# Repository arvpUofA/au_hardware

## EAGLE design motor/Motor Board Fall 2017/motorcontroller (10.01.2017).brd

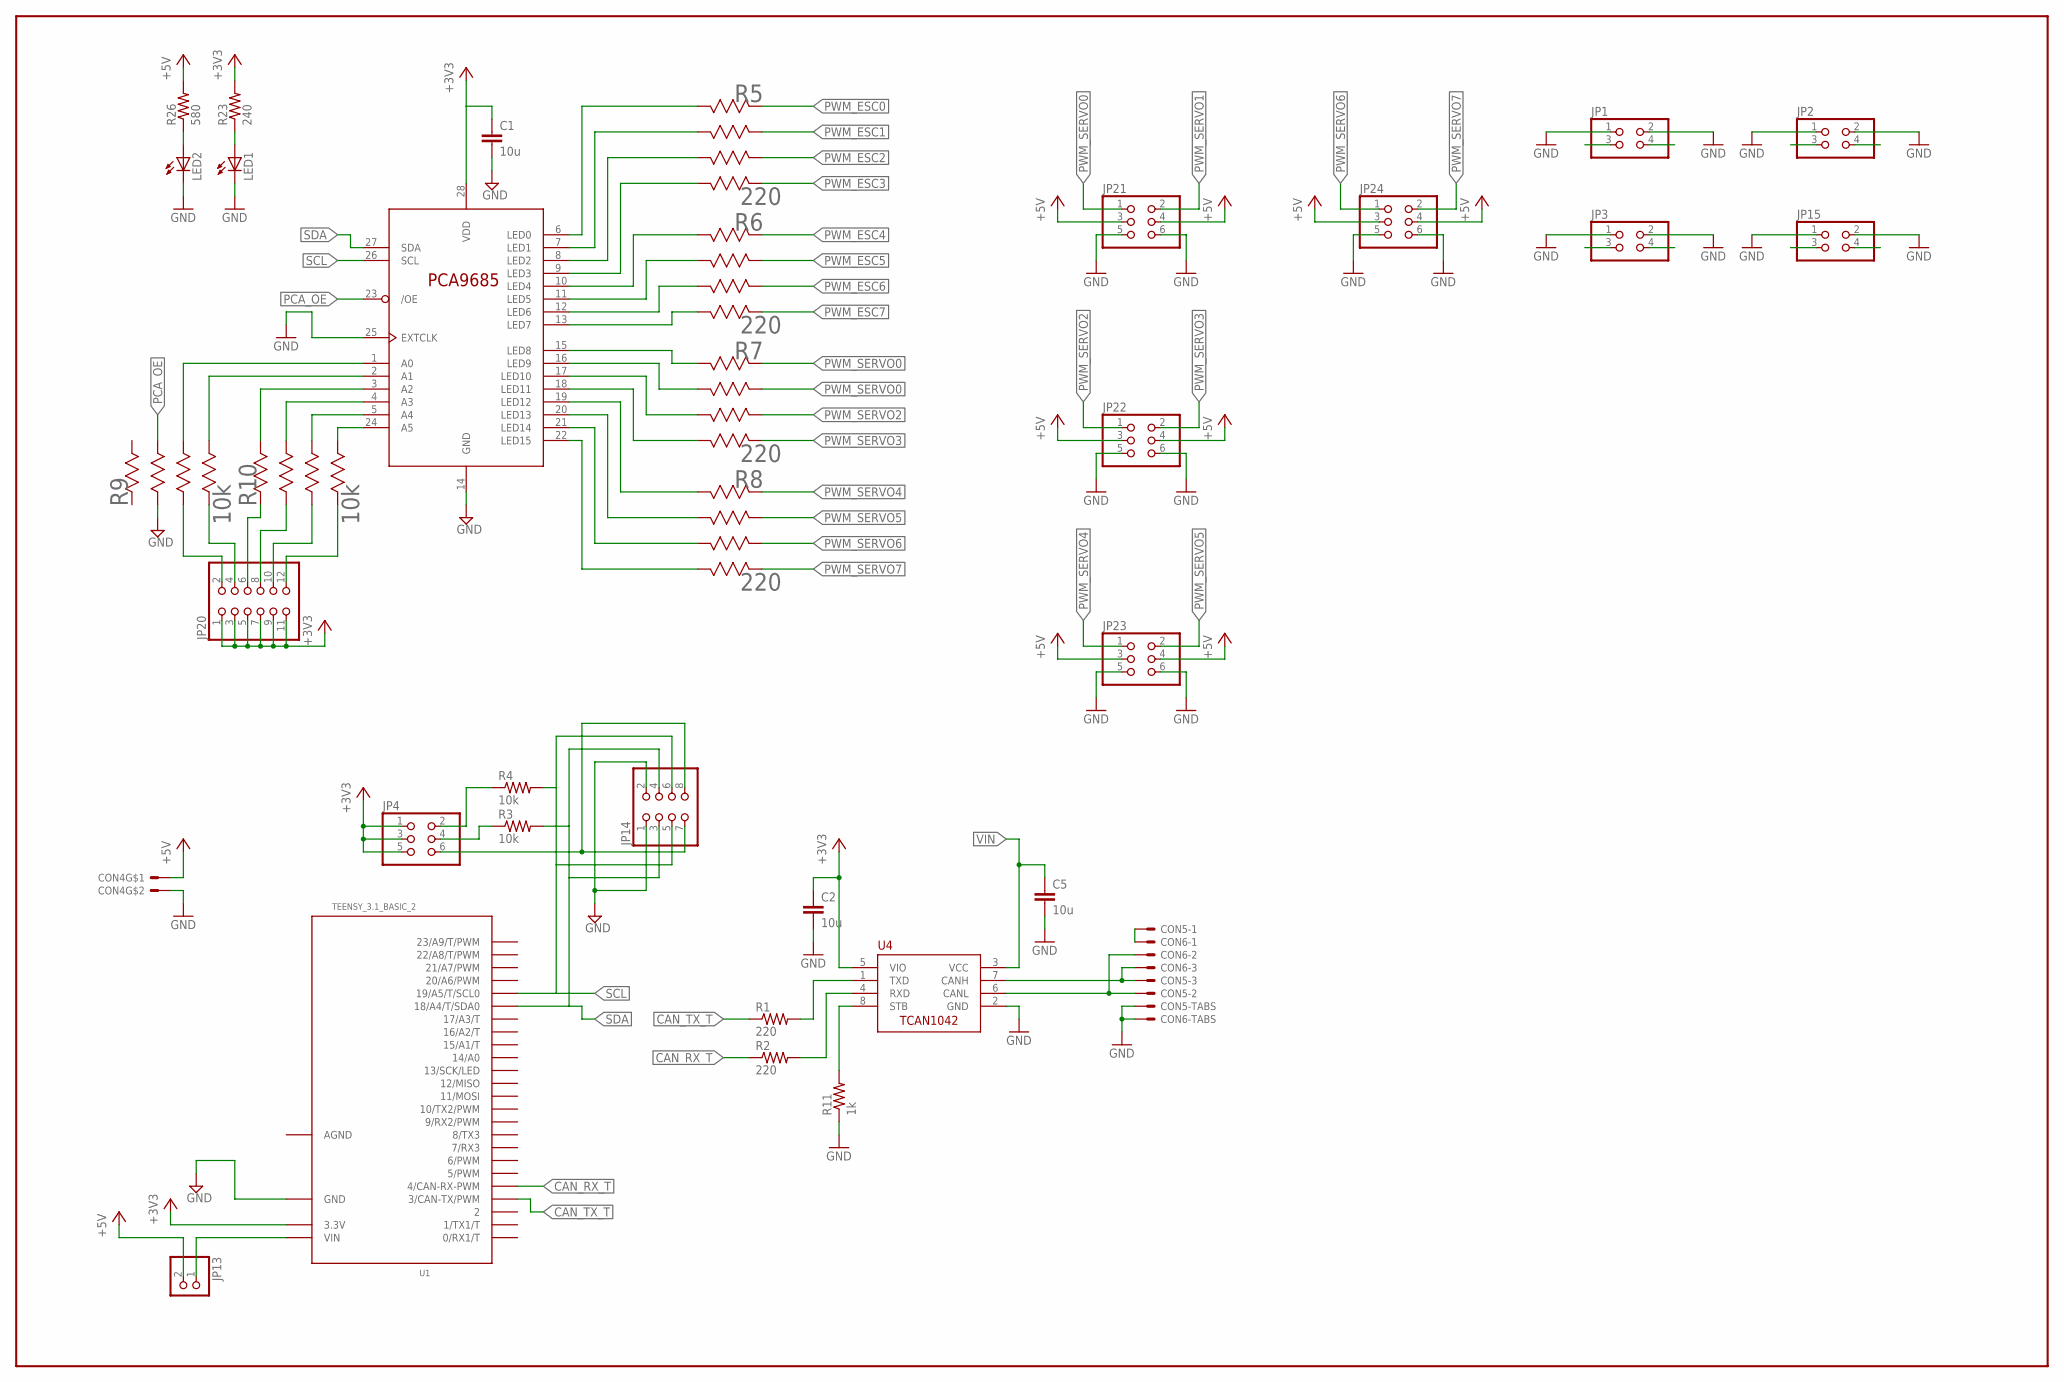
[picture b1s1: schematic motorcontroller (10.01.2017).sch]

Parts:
C1, C2, C5: 10u; C0805
CON4: MOLEX_5566-2; 5566-2
CON5, CON6: S3B-PH-SM4-TB
JP1, JP2, JP3, JP15: PINHD-2X2; 2X02
JP4, JP21, JP22, JP23, JP24: PINHD-2X3; 2X03
JP13: PINHD-1X2; 1X02
JP14: PINHD-2X4; 2X04
JP20: PINHD-2X6; 2X06
LED1, LED2: LEDCHIPLED_1206; CHIPLED_1206
R1, R2: 220; R0805
R3, R4: 10k; R1206
R5, R6, R7, R8: 220; EXBV8V-M
R9, R10: 10k; EXBV8V-M
R11: 1k; R0805
R23: 240; R1206
R26: 580; R1206
U1: TEENSY_3.1_BASIC_2
U2: PCA9685PW; TSSOP28
U4: TCAN1042HVDR; SO-8

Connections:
+3V3: C1.1, C2.1, JP4.1, JP4.3, JP4.5, JP20.1, JP20.3, JP20.5, JP20.7, JP20.9, JP20.11, R23.2, U1.3.3V, U2.28 (VDD), U4.5 (VIO)
+5V: CON4.1, JP13.2, JP21.3, JP21.4, JP22.3, JP22.4, JP23.3, JP23.4, JP24.3, JP24.4, R26.2
A0+1: JP20.2, R9.3 (35)
A1+1: JP20.4, R9.4 (47)
A2+1: JP20.6, R10.1 (11)
A3+1: JP20.8, R10.2 (23)
A4+1: JP20.10, R10.3 (35)
A5: JP20.12, R10.4 (47)
A6: R10.5 (58), U2.24 (A5)
A7: R10.6 (66), U2.5 (A4)
A8: R10.7 (74), U2.4 (A3)
A9: R10.8 (82), U2.3 (A2)
A10: R9.5 (58), U2.2 (A1)
A11: R9.6 (66), U2.1 (A0)
AGND: U1.AGND
CANH1: CON5.P$3, CON6.P$3, U4.7 (CANH)
CANL1: CON5.P$2, CON6.P$2, U4.6 (CANL)
CANSH1: CON5.P$1, CON6.P$1
CAN_RX1: R2.2, U4.4 (RXD)
CAN_RX_T: R2.1, U1.4 (4/CAN-RX-PWM)
CAN_TX2: R1.2, U4.1 (TXD)
CAN_TX_T: R1.1, U1.3 (3/CAN-TX/PWM)
GND: C1.2, C2.2, C5.2, CON4.2, CON5.P$4, CON5.P$5, CON6.P$4, CON6.P$5, JP1.1, JP1.2, JP2.1, JP2.2, JP3.1, JP3.2, JP14.1, JP14.2, JP15.1, JP15.2, JP21.5, JP21.6, JP22.5, JP22.6, JP23.5, JP23.6, JP24.5, JP24.6, LED1.C, LED2.C, R9.2 (23), R11.1, U1.GND, U2.14 (GND), U2.25 (EXTCLK), U4.2 (GND)
I2C_3V1: JP4.6, JP14.7, JP14.8
unnamed: LED1.A, R23.1
unnamed: LED2.A, R26.1
PCA_OE: R9.7 (74), U2.23 (/OE)
PWM_CH16: R5.8 (82), U2.6 (LED0)
PWM_CH17: R5.7 (74), U2.7 (LED1)
PWM_CH18: R5.6 (66), U2.8 (LED2)
PWM_CH19: R5.5 (58), U2.9 (LED3)
PWM_CH20: R6.8 (82), U2.10 (LED4)
PWM_CH21: R6.7 (74), U2.11 (LED5)
PWM_CH22: R6.6 (66), U2.12 (LED6)
PWM_CH23: R6.5 (58), U2.13 (LED7)
PWM_CH24: R7.8 (82), U2.15 (LED8)
PWM_CH25: R7.7 (74), U2.16 (LED9)
PWM_CH26: R7.6 (66), U2.17 (LED10)
PWM_CH27: R7.5 (58), U2.18 (LED11)
PWM_CH28: R8.8 (82), U2.19 (LED12)
PWM_CH29: R8.7 (74), U2.20 (LED13)
PWM_CH30: R8.6 (66), U2.21 (LED14)
PWM_CH31: R8.5 (58), U2.22 (LED15)
PWM_ESC0: JP15.4, R5.1 (11)
PWM_ESC1: JP15.3, R5.2 (23)
PWM_ESC2: JP1.4, R5.3 (35)
PWM_ESC3: JP1.3, R5.4 (47)
PWM_ESC4: JP2.4, R6.1 (11)
PWM_ESC5: JP2.3, R6.2 (23)
PWM_ESC6: JP3.4, R6.3 (35)
PWM_ESC7: JP3.3, R6.4 (47)
PWM_SERVO0: JP21.1, R7.1 (11)
PWM_SERVO1: JP21.2, R7.2 (23)
PWM_SERVO2: JP22.1, R7.3 (35)
PWM_SERVO3: JP22.2, R7.4 (47)
PWM_SERVO4: JP23.1, R8.1 (11)
PWM_SERVO5: JP23.2, R8.2 (23)
PWM_SERVO6: JP24.1, R8.3 (35)
PWM_SERVO7: JP24.2, R8.4 (47)
SCL: JP14.5, JP14.6, R4.2, U1.19/A5 (19/A5/T/SCL0), U2.26 (SCL)
SCL_3V1: JP4.2, R4.1
SDA: JP14.3, JP14.4, R3.2, U1.18/A4 (18/A4/T/SDA0), U2.27 (SDA)
SDA_3V1: JP4.4, R3.1
STB1: R11.2, U4.8 (STB)
VIN: C5.1, JP13.1, U1.VIN, U4.3 (VCC)

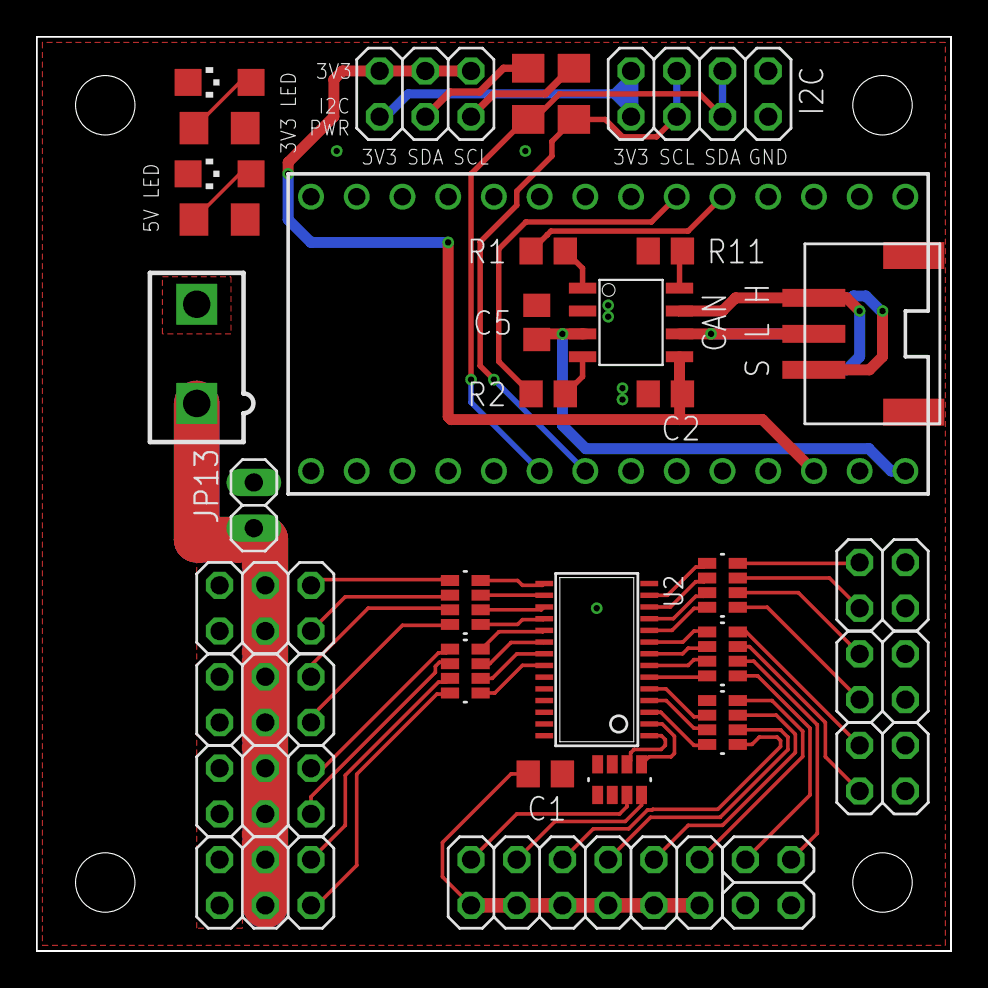
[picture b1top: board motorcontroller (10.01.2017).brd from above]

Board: 2 copper layers, 50.8 x 50.8 mm, 42 parts (1 on the bottom side), 64 nets.

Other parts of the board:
U$2, U$3, U$4, U$5: STAND-OFF
U$11: LETTER_L
U$12: DOCFIELD

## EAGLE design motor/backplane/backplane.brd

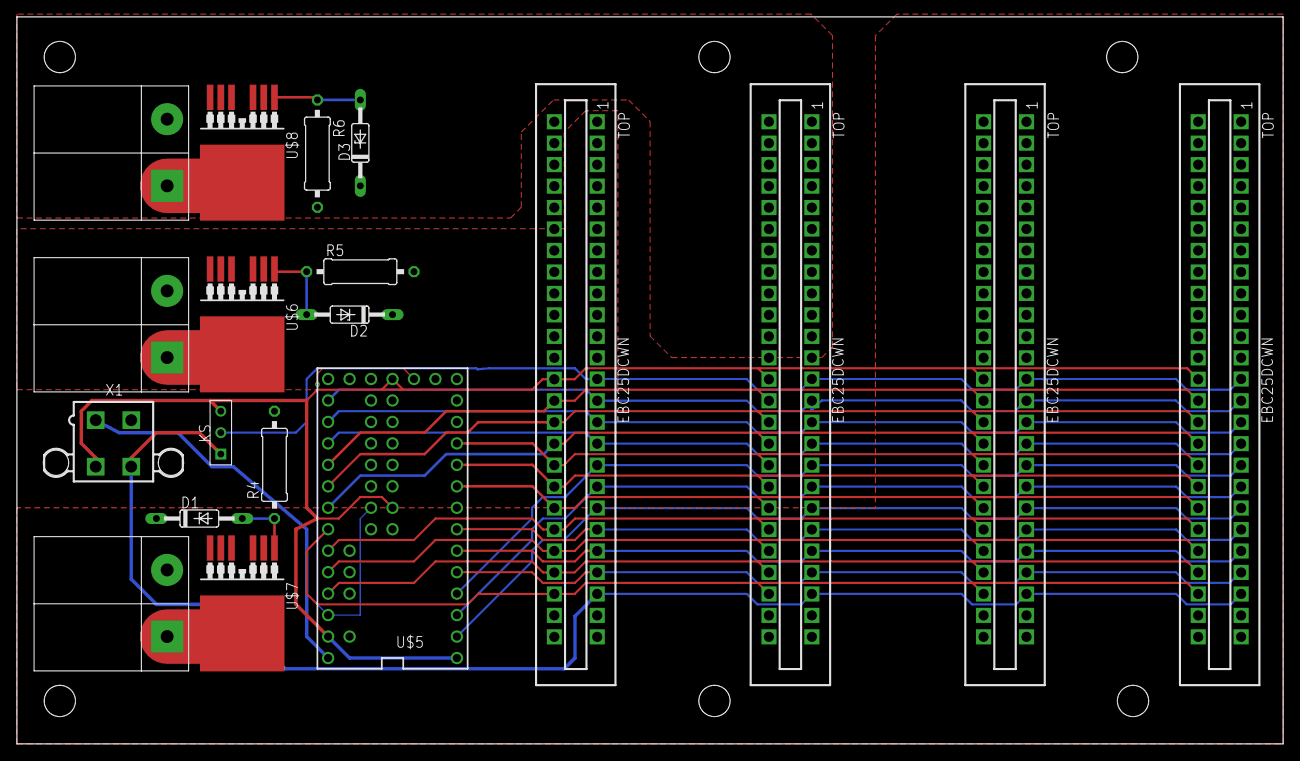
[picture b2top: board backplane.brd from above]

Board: 2 copper layers, 149.8 x 86.0 mm, 19 parts (0 on the bottom side), 34 nets.

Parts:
D1, D2, D3: BZX55; DO35Z10
R4, R5, R6: 100k; 0309/12
U$1, U$2, U$3: AND_PWR
U$4, U$9, U$10, U$11: CONN_50PIN
U$5: TEENSY_3.1-3.2_ALL_PINS&PADS; TEENSY_3.0-3.2_ALL_PINS_&_PADS
U$6, U$7, U$8: IPB180P04P4L-02; PG-TO263-7-3
U$12: KILL_SW
X1: 5566-4

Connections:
3.3V: U$4.A23, U$9.A23, U$10.A23, U$11.A23, U$12.P$1, X1.4
5V: U$5.VIN, X1.1
AGND: R4.2, R5.2, R6.2, U$1.GND, U$2.GND, U$3.GND, U$4.B1, U$4.B2, U$4.B3, U$4.B4, U$4.B5, U$4.B6, U$4.B7, U$4.B8, U$4.B9, U$4.B10, U$4.B11, U$4.B12, U$9.B1, U$9.B2, U$9.B3, U$9.B4, U$9.B5, U$9.B6, U$9.B7, U$9.B8, U$9.B9, U$9.B10, U$9.B11, U$9.B12, U$10.B1, U$10.B2, U$10.B3, U$10.B4, U$10.B5, U$10.B6, U$10.B7, U$10.B8, U$10.B9, U$10.B10, U$10.B11, U$10.B12, U$11.B1, U$11.B2, U$11.B3, U$11.B4, U$11.B5, U$11.B6, U$11.B7, U$11.B8, U$11.B9, U$11.B10, U$11.B11, U$11.B12
BAT+0: U$3.PWR, U$8.8
BAT+1: U$2.PWR, U$6.8
BAT+2: U$1.PWR, U$7.8
CS_X0: U$4.A16, U$5.16/A2, U$9.A16, U$10.A16, U$11.A16
CS_X1: U$4.B16, U$5.19/A5, U$9.B16, U$10.B16, U$11.B16
CS_Y0: U$4.A15, U$5.15/A1, U$9.A15, U$10.A15, U$11.A15
CS_Y1: U$4.B15, U$5.18/A4, U$9.B15, U$10.B15, U$11.B15
CS_Z0: U$4.A14, U$5.14/A0, U$9.A14, U$10.A14, U$11.A14
CS_Z1: U$4.B14, U$5.17/A3, U$9.B14, U$10.B14, U$11.B14
DIR_X0: U$4.A19, U$5.0, U$9.A19, U$10.A19, U$11.A19
DIR_X1: U$4.B19, U$5.7, U$9.B19, U$10.B19, U$11.B19
DIR_Y0: U$4.A18, U$5.1, U$9.A18, U$10.A18, U$11.A18
DIR_Y1: U$4.B18, U$5.8, U$9.B18, U$10.B18, U$11.B18
DIR_Z0: U$4.A17, U$5.2, U$9.A17, U$10.A17, U$11.A17
DIR_Z1: U$4.B17, U$5.9, U$9.B17, U$10.B17, U$11.B17
EN: U$4.B23, U$5.20/A6, U$9.B23, U$10.B23, U$11.B23
GND: U$4.B13, U$5.AGND, U$5.GND, U$5.GND1, U$5.GND2, U$9.B13, U$10.B13, U$11.B13, U$12.P$3, X1.3
KS: U$4.A13, U$9.A13, U$10.A13, U$11.A13, U$12.P$2
unnamed: U$5.3.3V, U$5.3.3V1, U$5.3.3V2
unnamed: D3.A, R6.1, U$8.1
unnamed: D2.A, R5.1, U$6.1
unnamed: D1.A, R4.1, U$7.1
PWM_X0: U$4.A22, U$5.3, U$9.A22, U$10.A22, U$11.A22
PWM_X1: U$4.B22, U$5.23/A9, U$9.B22, U$10.B22, U$11.B22
PWM_Y0: U$4.A21, U$5.4, U$9.A21, U$10.A21, U$11.A21
PWM_Y1: U$4.B21, U$5.22/A8, U$9.B21, U$10.B21, U$11.B21
PWM_Z0: U$4.A20, U$5.5, U$9.A20, U$10.A20, U$11.A20
PWM_Z1: U$4.B20, U$5.21/A7, U$9.B20, U$10.B20, U$11.B20
PWR0: D3.C, U$8.2, U$8.3, U$8.5, U$8.6, U$8.7, U$9.A1, U$9.A2, U$9.A3, U$9.A4, U$9.A5, U$9.A6, U$9.A7, U$9.A8, U$9.A9, U$9.A10, U$9.A11, U$9.A12
PWR1: D2.C, U$4.A1, U$4.A2, U$4.A3, U$4.A4, U$4.A5, U$4.A6, U$4.A7, U$4.A8, U$4.A9, U$4.A10, U$4.A11, U$4.A12, U$6.2, U$6.3, U$6.5, U$6.6, U$6.7
PWR2: D1.C, U$7.2, U$7.3, U$7.5, U$7.6, U$7.7, U$10.A1, U$10.A2, U$10.A3, U$10.A4, U$10.A5, U$10.A6, U$10.A7, U$10.A8, U$10.A9, U$10.A10, U$10.A11, U$10.A12

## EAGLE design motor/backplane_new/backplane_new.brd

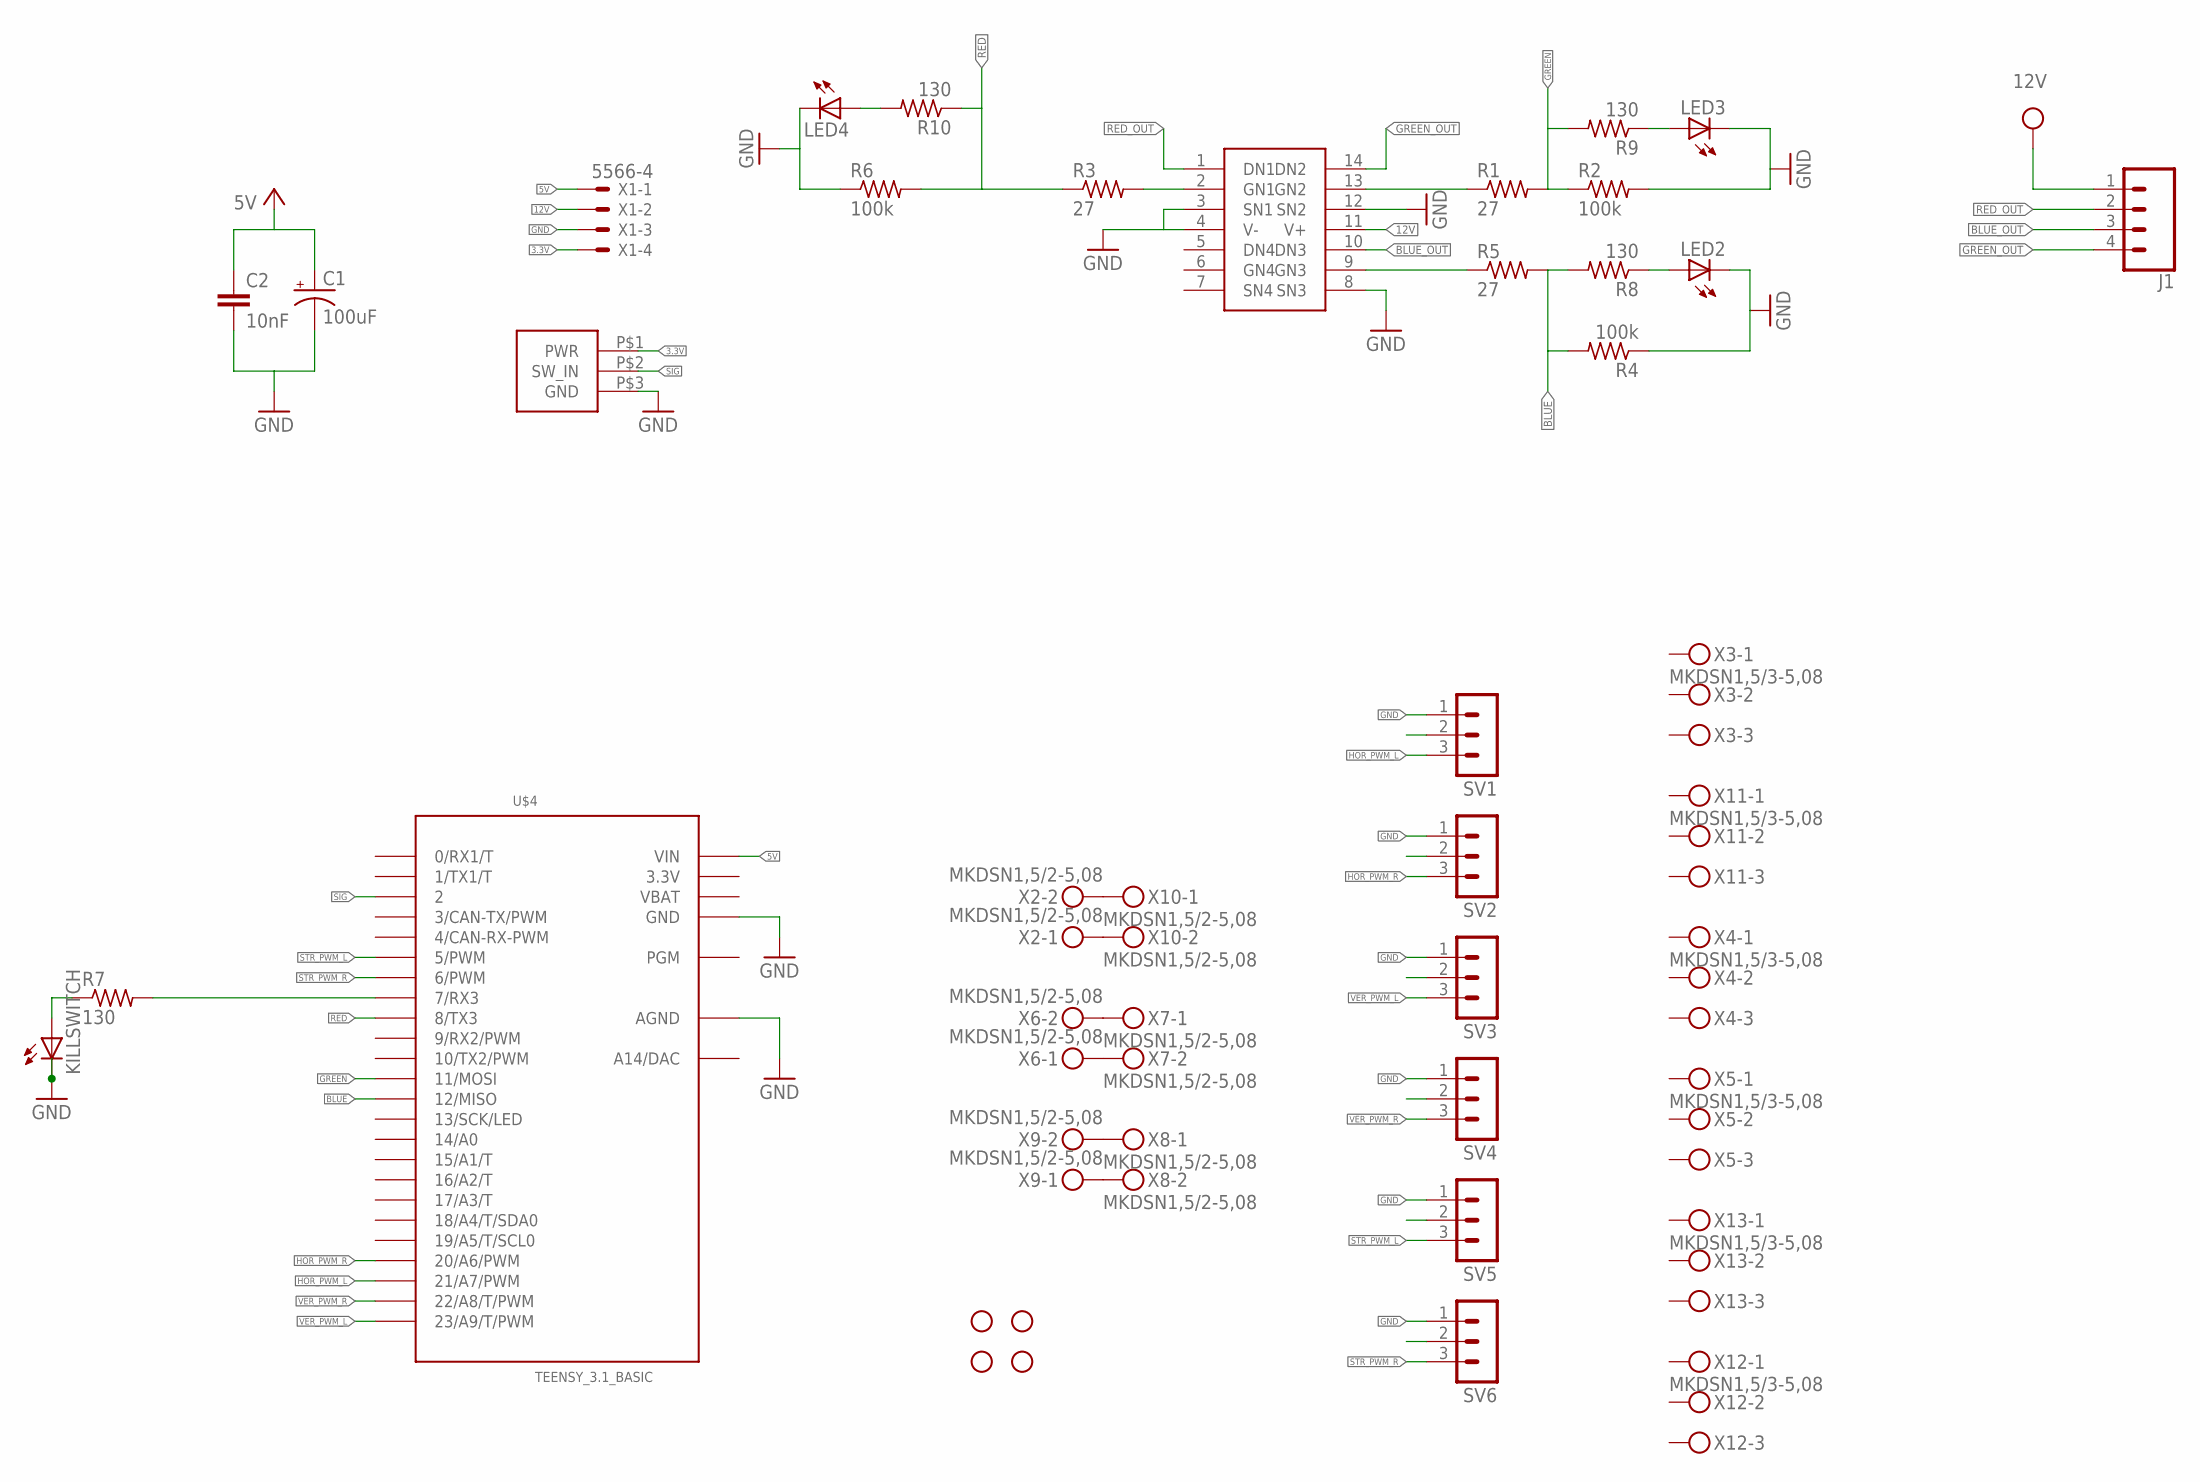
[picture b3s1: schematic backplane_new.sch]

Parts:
C1: 100uF; E5-10,5
C2: 10nF; C0805
H1, H2, H3, H5: STAND-OFF
J1: CONN_04POLAR; MOLEX-1X4
KILLSWITCH: LED5MM
LED2, LED3, LED4: LEDCHIP-LED0805; CHIP-LED0805
R1, R3, R5: 27; R0805
R2, R4, R6: 100k; R0805
R7, R8, R9, R10: 130; R0805
SV1, SV2, SV3, SV4, SV5, SV6: MA03-1
U$2: KILL_SW
U$3: ALD1160; DIL14
U$4: TEENSY_3.1_BASIC
X1: 5566-4
X2, X6, X7, X8, X9, X10: MKDSN1,5/2-5,08
X3, X4, X5, X11, X12, X13: MKDSN1,5/3-5,08

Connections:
3.3V: U$2.P$1 (PWR), U$4.3.3V, U$4.3.3V1 (3.3V), X1.4
5V: C1.+, C2.1, U$4.VIN, X1.1
12V: J1.1, U$3.11 (V+), X1.2
BLUE: R4.2, R5.2, R8.2, U$4.12 (12/MISO)
BLUE_OUT: J1.3, U$3.10 (DN3)
GND: C1.-, C2.2, KILLSWITCH.K (C), LED2.C, LED3.C, LED4.C, R2.2, R4.1, R6.1, SV1.1, SV2.1, SV3.1, SV4.1, SV5.1, SV6.1, U$2.P$3 (GND), U$3.3 (SN1), U$3.4 (V-), U$3.8 (SN3), U$3.12 (SN2), U$4.AGND, U$4.GND, U$4.GND1 (GND), X1.3
GREEN: R1.2, R2.1, R9.2, U$4.11 (11/MOSI)
GREEN_OUT: J1.4, U$3.14 (DN2)
HOR_PWM_L: SV1.3, U$4.21/A7 (21/A7/PWM)
HOR_PWM_R: SV2.3, U$4.20/A6 (20/A6/PWM)
unnamed: X2.1, X10.2
unnamed: X2.2, X10.1
unnamed: X6.2, X7.1
unnamed: X6.1, X7.2
unnamed: X8.2, X9.1
unnamed: X8.1, X9.2
unnamed: R7.2, U$4.7 (7/RX3)
unnamed: KILLSWITCH.A, R7.1
unnamed: R3.2, U$3.2 (GN1)
unnamed: R1.1, U$3.13 (GN2)
unnamed: R5.1, U$3.9 (GN3)
unnamed: LED2.A, R8.1
unnamed: LED4.A, R10.2
unnamed: LED3.A, R9.1
RED: R3.1, R6.2, R10.1, U$4.8 (8/TX3)
RED_OUT: J1.2, U$3.1 (DN1)
SIG: U$2.P$2 (SW_IN), U$4.2
STR_PWM_L: SV5.3, U$4.5 (5/PWM)
STR_PWM_R: SV6.3, U$4.6 (6/PWM)
VBAT: U$4.VBAT
VER_PWM_L: SV3.3, U$4.23/A9 (23/A9/T/PWM)
VER_PWM_R: SV4.3, U$4.22/A8 (22/A8/T/PWM)

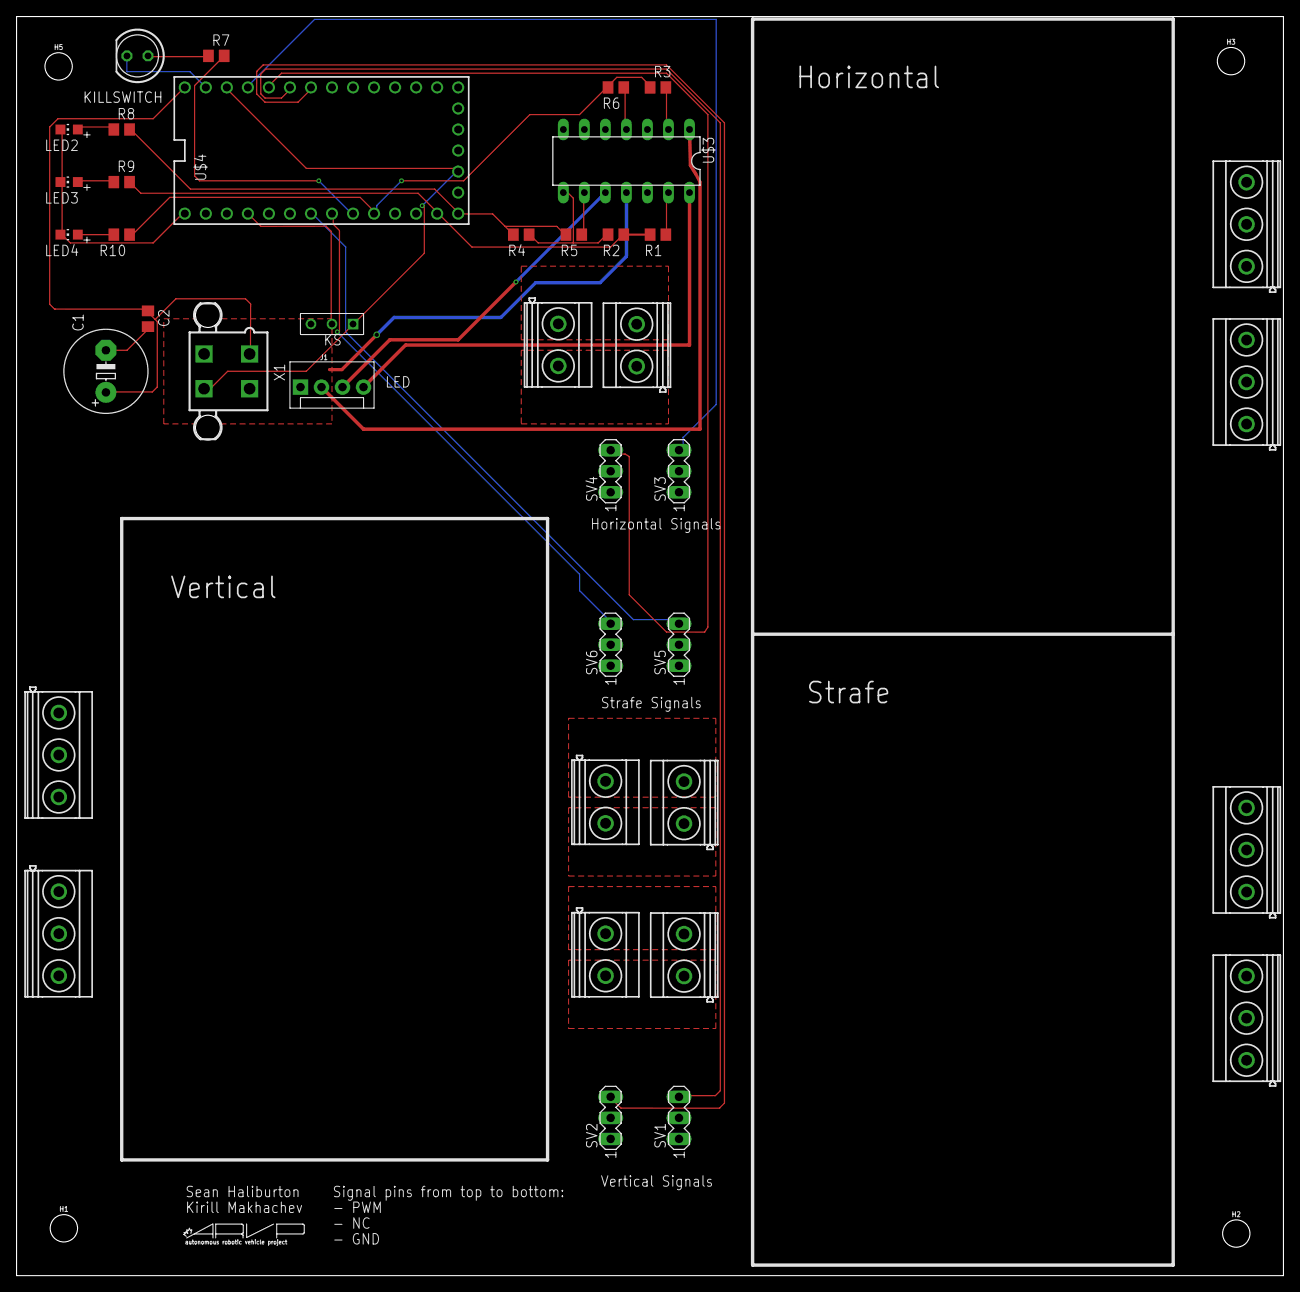
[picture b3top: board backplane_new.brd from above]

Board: 2 copper layers, 153.0 x 152.1 mm, 44 parts (0 on the bottom side), 31 nets.

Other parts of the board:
U$1: ARVP

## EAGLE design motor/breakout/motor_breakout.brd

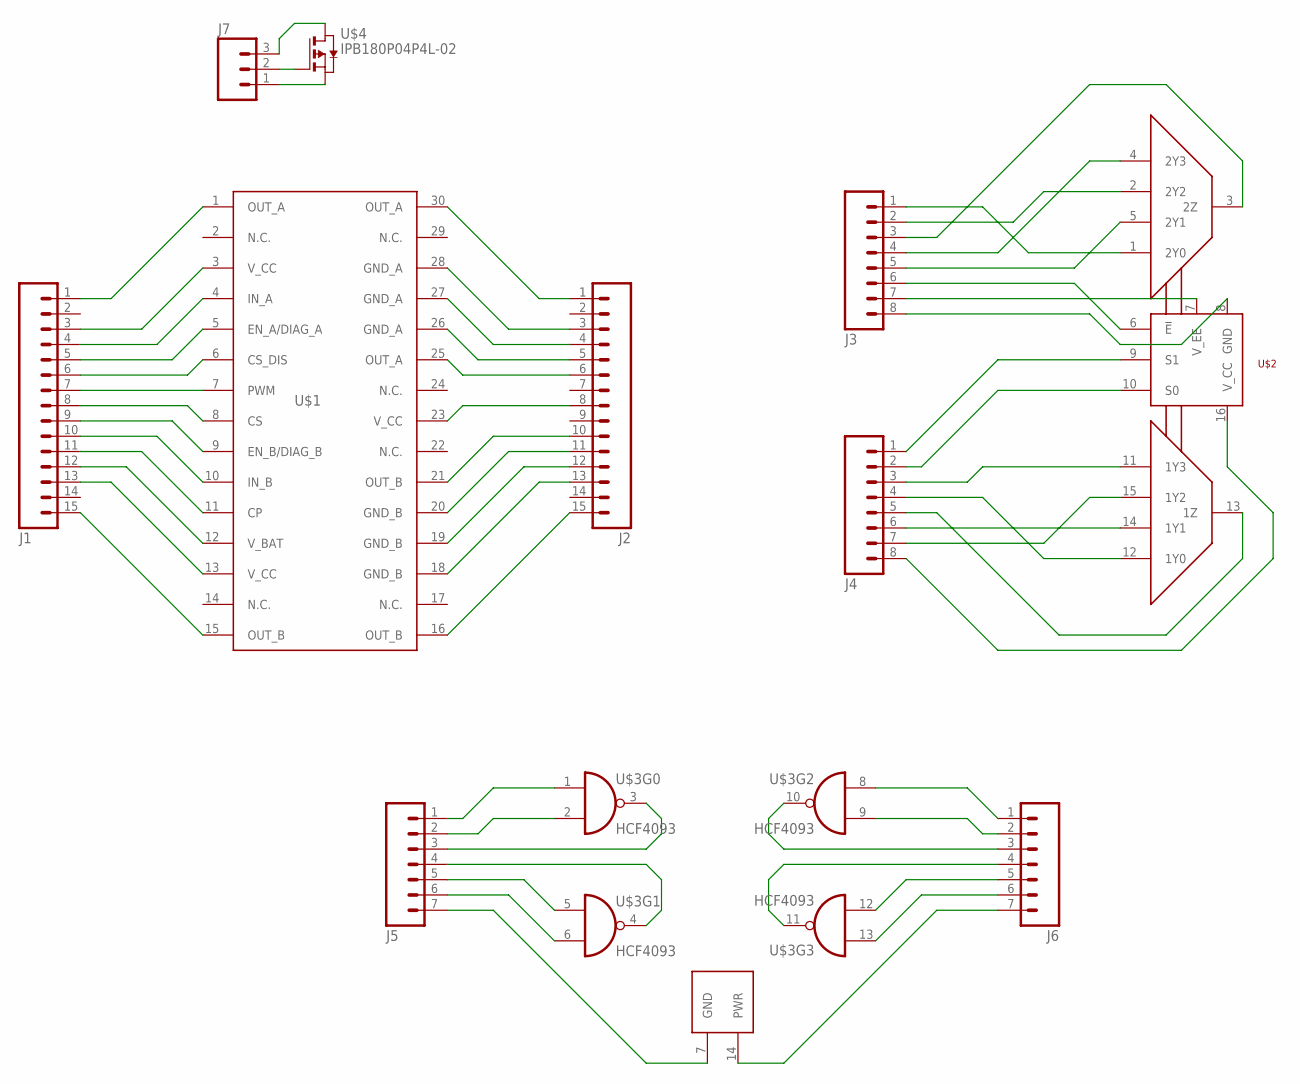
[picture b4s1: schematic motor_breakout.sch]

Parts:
J1, J2: M15; 1X15
J3, J4: M08SILK_FEMALE_PTH; 1X08
J5, J6: M07; 1X07
J7: M03PTH; 1X03
U$1: VNH5019A-E; MULTIPOWERSO-30
U$2: 74HC4052-Q100; SO16
U$3: HCF4093; SO14
U$4: IPB180P04P4L-02; PG-TO263-7-3

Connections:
GND_A: J2.3, J2.4, J2.5, U$1.26 (GND_A), U$1.27 (GND_A), U$1.28 (GND_A)
GND_B: J2.11, J2.12, J2.13, U$1.18 (GND_B), U$1.19 (GND_B), U$1.20 (GND_B)
unnamed: J1.7, U$1.7 (PWM)
unnamed: J7.2, U$4.1 (G)
unnamed: J1.8, U$1.8 (CS)
unnamed: J1.6, U$1.6 (CS_DIS)
unnamed: J1.9, U$1.9 (EN_B/DIAG_B)
unnamed: J1.5, U$1.5 (EN_A/DIAG_A)
unnamed: J1.4, U$1.4 (IN_A)
unnamed: J1.10, U$1.10 (IN_B)
unnamed: J1.11, U$1.11 (CP)
unnamed: J1.12, U$1.12 (V_BAT)
unnamed: J3.1, U$2.1 (2Y0)
unnamed: J3.2, U$2.2 (2Y2)
unnamed: J3.3, U$2.3 (2Z)
unnamed: J3.4, U$2.4 (2Y3)
unnamed: J3.5, U$2.5 (2Y1)
unnamed: J3.6, U$2.6 (!E)
unnamed: J3.7, U$2.7 (V_EE)
unnamed: J3.8, U$2.8 (GND)
unnamed: J4.1, U$2.9 (S1)
unnamed: J4.2, U$2.10 (S0)
unnamed: J4.3, U$2.11 (1Y3)
unnamed: J4.4, U$2.12 (1Y0)
unnamed: J4.5, U$2.13 (1Z)
unnamed: J4.6, U$2.14 (1Y1)
unnamed: J4.7, U$2.15 (1Y2)
unnamed: J4.8, U$2.16 (V_CC)
unnamed: J5.1, U$3.1 (I0)
unnamed: J5.2, U$3.2 (I1)
unnamed: J5.3, U$3.3 (O)
unnamed: J5.4, U$3.4 (O)
unnamed: J5.5, U$3.5 (I0)
unnamed: J5.6, U$3.6 (I1)
unnamed: J5.7, U$3.7 (GND)
unnamed: J6.1, U$3.8 (I0)
unnamed: J6.2, U$3.9 (I1)
unnamed: J6.3, U$3.10 (O)
unnamed: J6.4, U$3.11 (O)
unnamed: J6.5, U$3.12 (I1)
unnamed: J6.6, U$3.13 (I0)
unnamed: J6.7, U$3.14 (PWR)
unnamed: J7.1, U$4.2 (S), U$4.3 (S), U$4.5 (S), U$4.6 (S), U$4.7 (S)
unnamed: J7.3, U$4.8 (D)
OUT_A: J1.1, J2.1, J2.6, U$1.1 (OUT_A), U$1.25 (OUT_A), U$1.30 (OUT_A)
OUT_B: J1.15, J2.10, J2.15, U$1.15 (OUT_B), U$1.16 (OUT_B), U$1.21 (OUT_B)
VCC: J1.3, J1.13, J2.8, U$1.3 (V_CC), U$1.13 (V_CC), U$1.23 (V_CC)

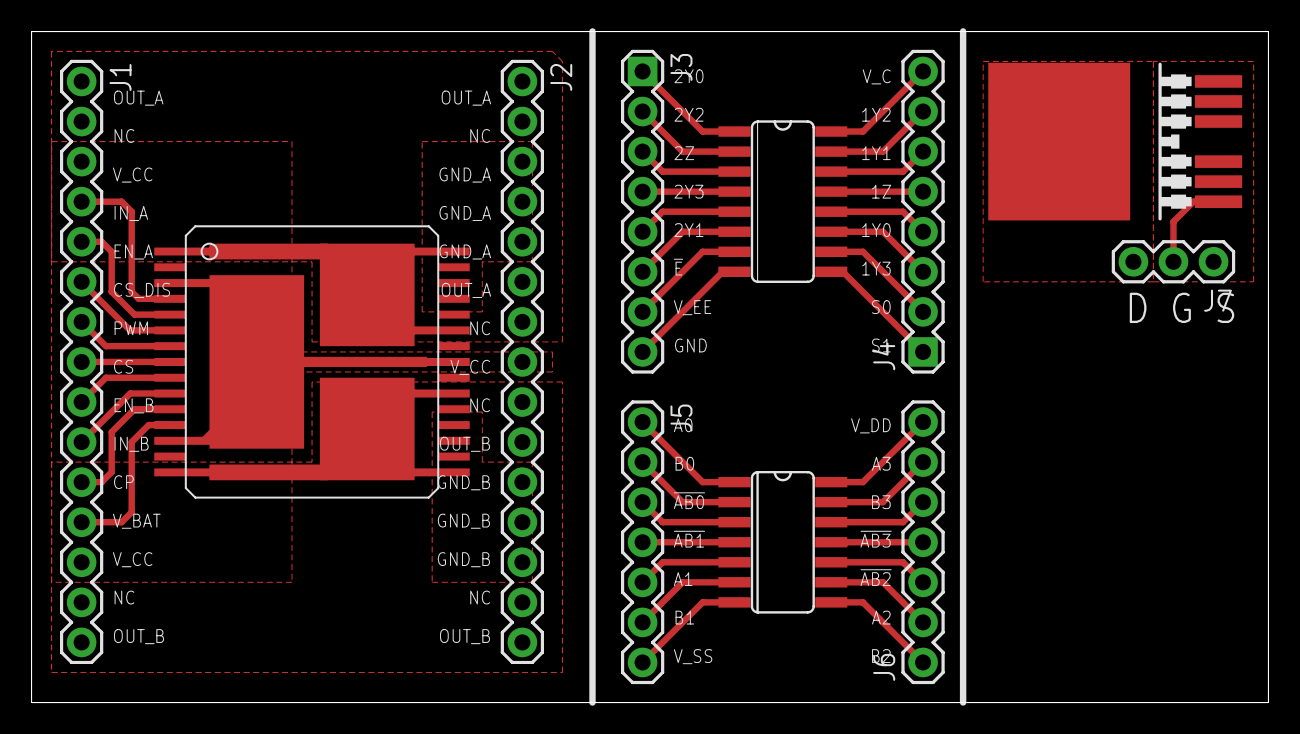
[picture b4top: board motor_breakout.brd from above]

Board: 2 copper layers, 78.4 x 42.5 mm, 11 parts (0 on the bottom side), 47 nets.

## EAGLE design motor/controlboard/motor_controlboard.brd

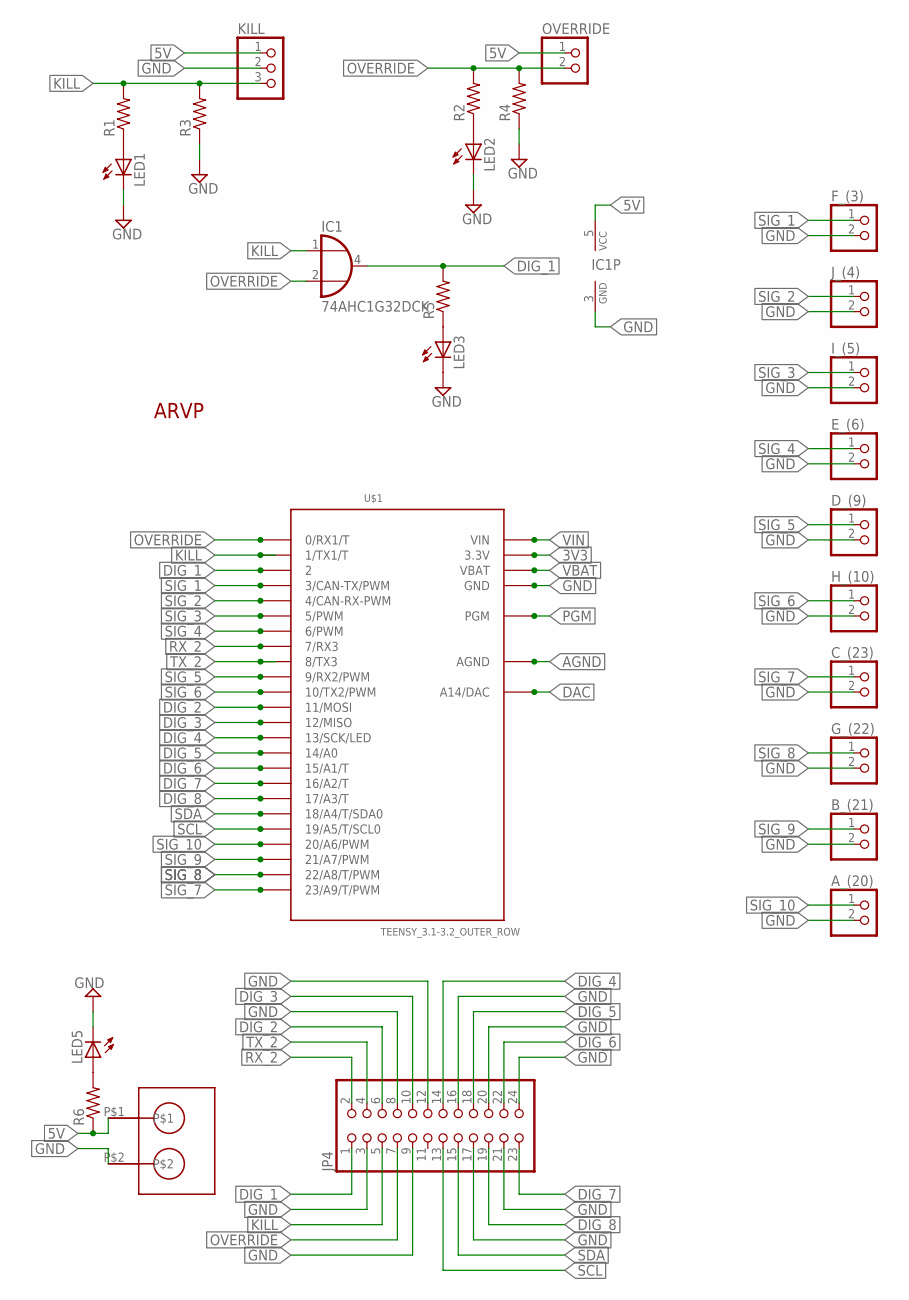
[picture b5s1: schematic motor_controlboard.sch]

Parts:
A_(20): PINHD-1X2; 1X02
B_(21): PINHD-1X2; 1X02
C_(23): PINHD-1X2; 1X02
D_(9): PINHD-1X2; 1X02
E_(6): PINHD-1X2; 1X02
F_(3): PINHD-1X2; 1X02
G_(22): PINHD-1X2; 1X02
H_(10): PINHD-1X2; 1X02
IC1: 74AHC1G32DCK; SC70-5
I_(5): PINHD-1X2; 1X02
JP4: PINHD-2X12; 2X12
J_(4): PINHD-1X2; 1X02
KILL: PINHD-1X3; 1X03
LED1, LED2, LED3, LED5: LEDCHIP-LED0805; CHIP-LED0805
OVERRIDE: PINHD-1X2; 1X02
R1, R2, R3, R4, R5, R6: R-US_R0805; R0805
U$1: TEENSY_3.1-3.2_OUTER_ROW; TEENSY_3.0-3.2&LC_OUTER_ROW
U$2: ARVP_LOGO; ARVP
U$3: ARVP_MOLEX_FEMALE

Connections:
3V3: U$1.3.3V, U$1.3.3V1 (3.3V)
5V: IC1.5 (VCC), KILL.1, OVERRIDE.1, R6.1, U$3.P$1
AGND: U$1.AGND
DAC: U$1.RESET/DAC (A14/DAC)
DIG_1: IC1.4 (O), JP4.1, R5.2, U$1.2
DIG_2: JP4.6, U$1.11 (11/MOSI)
DIG_3: JP4.10, U$1.12 (12/MISO)
DIG_4: JP4.14, U$1.13 (13/SCK/LED)
DIG_5: JP4.18, U$1.14/A0
DIG_6: JP4.22, U$1.15/A1 (15/A1/T)
DIG_7: JP4.23, U$1.16/A2 (16/A2/T)
DIG_8: JP4.19, U$1.17/A3 (17/A3/T)
GND: A_(20).2, B_(21).2, C_(23).2, D_(9).2, E_(6).2, F_(3).2, G_(22).2, H_(10).2, IC1.3 (GND), I_(5).2, JP4.3, JP4.8, JP4.9, JP4.12, JP4.16, JP4.17, JP4.20, JP4.21, JP4.24, J_(4).2, KILL.2, LED1.C, LED2.C, LED3.C, LED5.C, R3.1, R4.1, U$1.GND, U$1.GND1 (GND), U$3.P$2
KILL: IC1.1 (I0), JP4.5, KILL.3, R1.2, R3.2, U$1.1 (1/TX1/T)
unnamed: LED1.A, R1.1
unnamed: LED2.A, R2.1
unnamed: LED3.A, R5.1
unnamed: LED5.A, R6.2
OVERRIDE: IC1.2 (I1), JP4.7, OVERRIDE.2, R2.2, R4.2, U$1.0 (0/RX1/T)
PGM: U$1.PGM
RX_2: JP4.2, U$1.7 (7/RX3)
SCL: JP4.13, U$1.19/A5 (19/A5/T/SCL0)
SDA: JP4.15, U$1.18/A4 (18/A4/T/SDA0)
SIG_1: F_(3).1, U$1.3 (3/CAN-TX/PWM)
SIG_2: J_(4).1, U$1.4 (4/CAN-RX-PWM)
SIG_3: I_(5).1, U$1.5 (5/PWM)
SIG_4: E_(6).1, U$1.6 (6/PWM)
SIG_5: D_(9).1, U$1.9 (9/RX2/PWM)
SIG_6: H_(10).1, U$1.10 (10/TX2/PWM)
SIG_7: C_(23).1, U$1.23/A9 (23/A9/T/PWM)
SIG_8: G_(22).1, U$1.22/A8 (22/A8/T/PWM)
SIG_9: B_(21).1, U$1.21/A7 (21/A7/PWM)
SIG_10: A_(20).1, U$1.20/A6 (20/A6/PWM)
TX_2: JP4.4, U$1.8 (8/TX3)
VBAT: U$1.VBAT
VIN: U$1.VIN

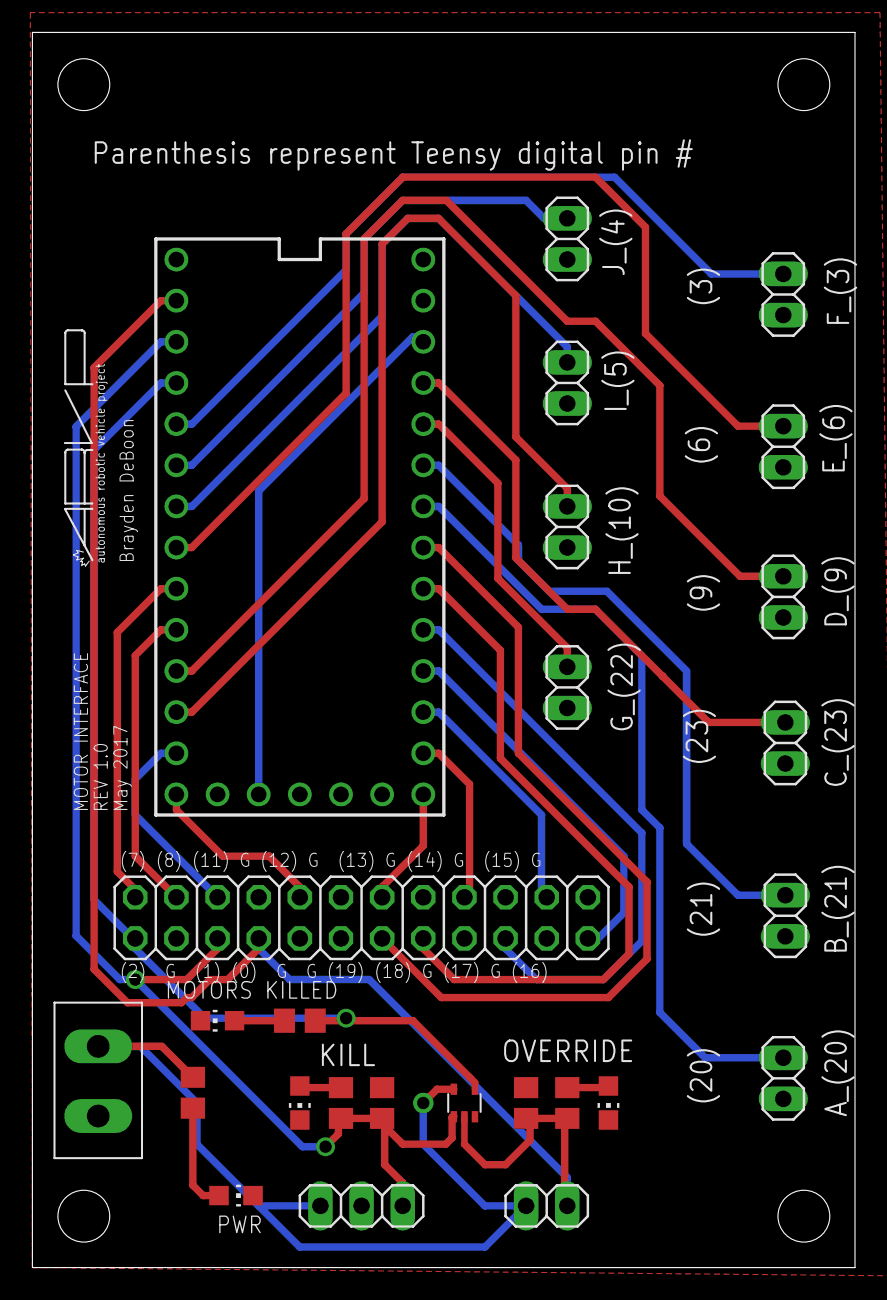
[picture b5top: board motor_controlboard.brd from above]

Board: 2 copper layers, 50.8 x 76.3 mm, 27 parts (0 on the bottom side), 31 nets.

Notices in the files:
parts and their libraries:
SparkFun-Connectors: Licensing: Creative Commons ShareAlike 4.0 International - https://creativecommons.org/licenses/by-sa/4.0
